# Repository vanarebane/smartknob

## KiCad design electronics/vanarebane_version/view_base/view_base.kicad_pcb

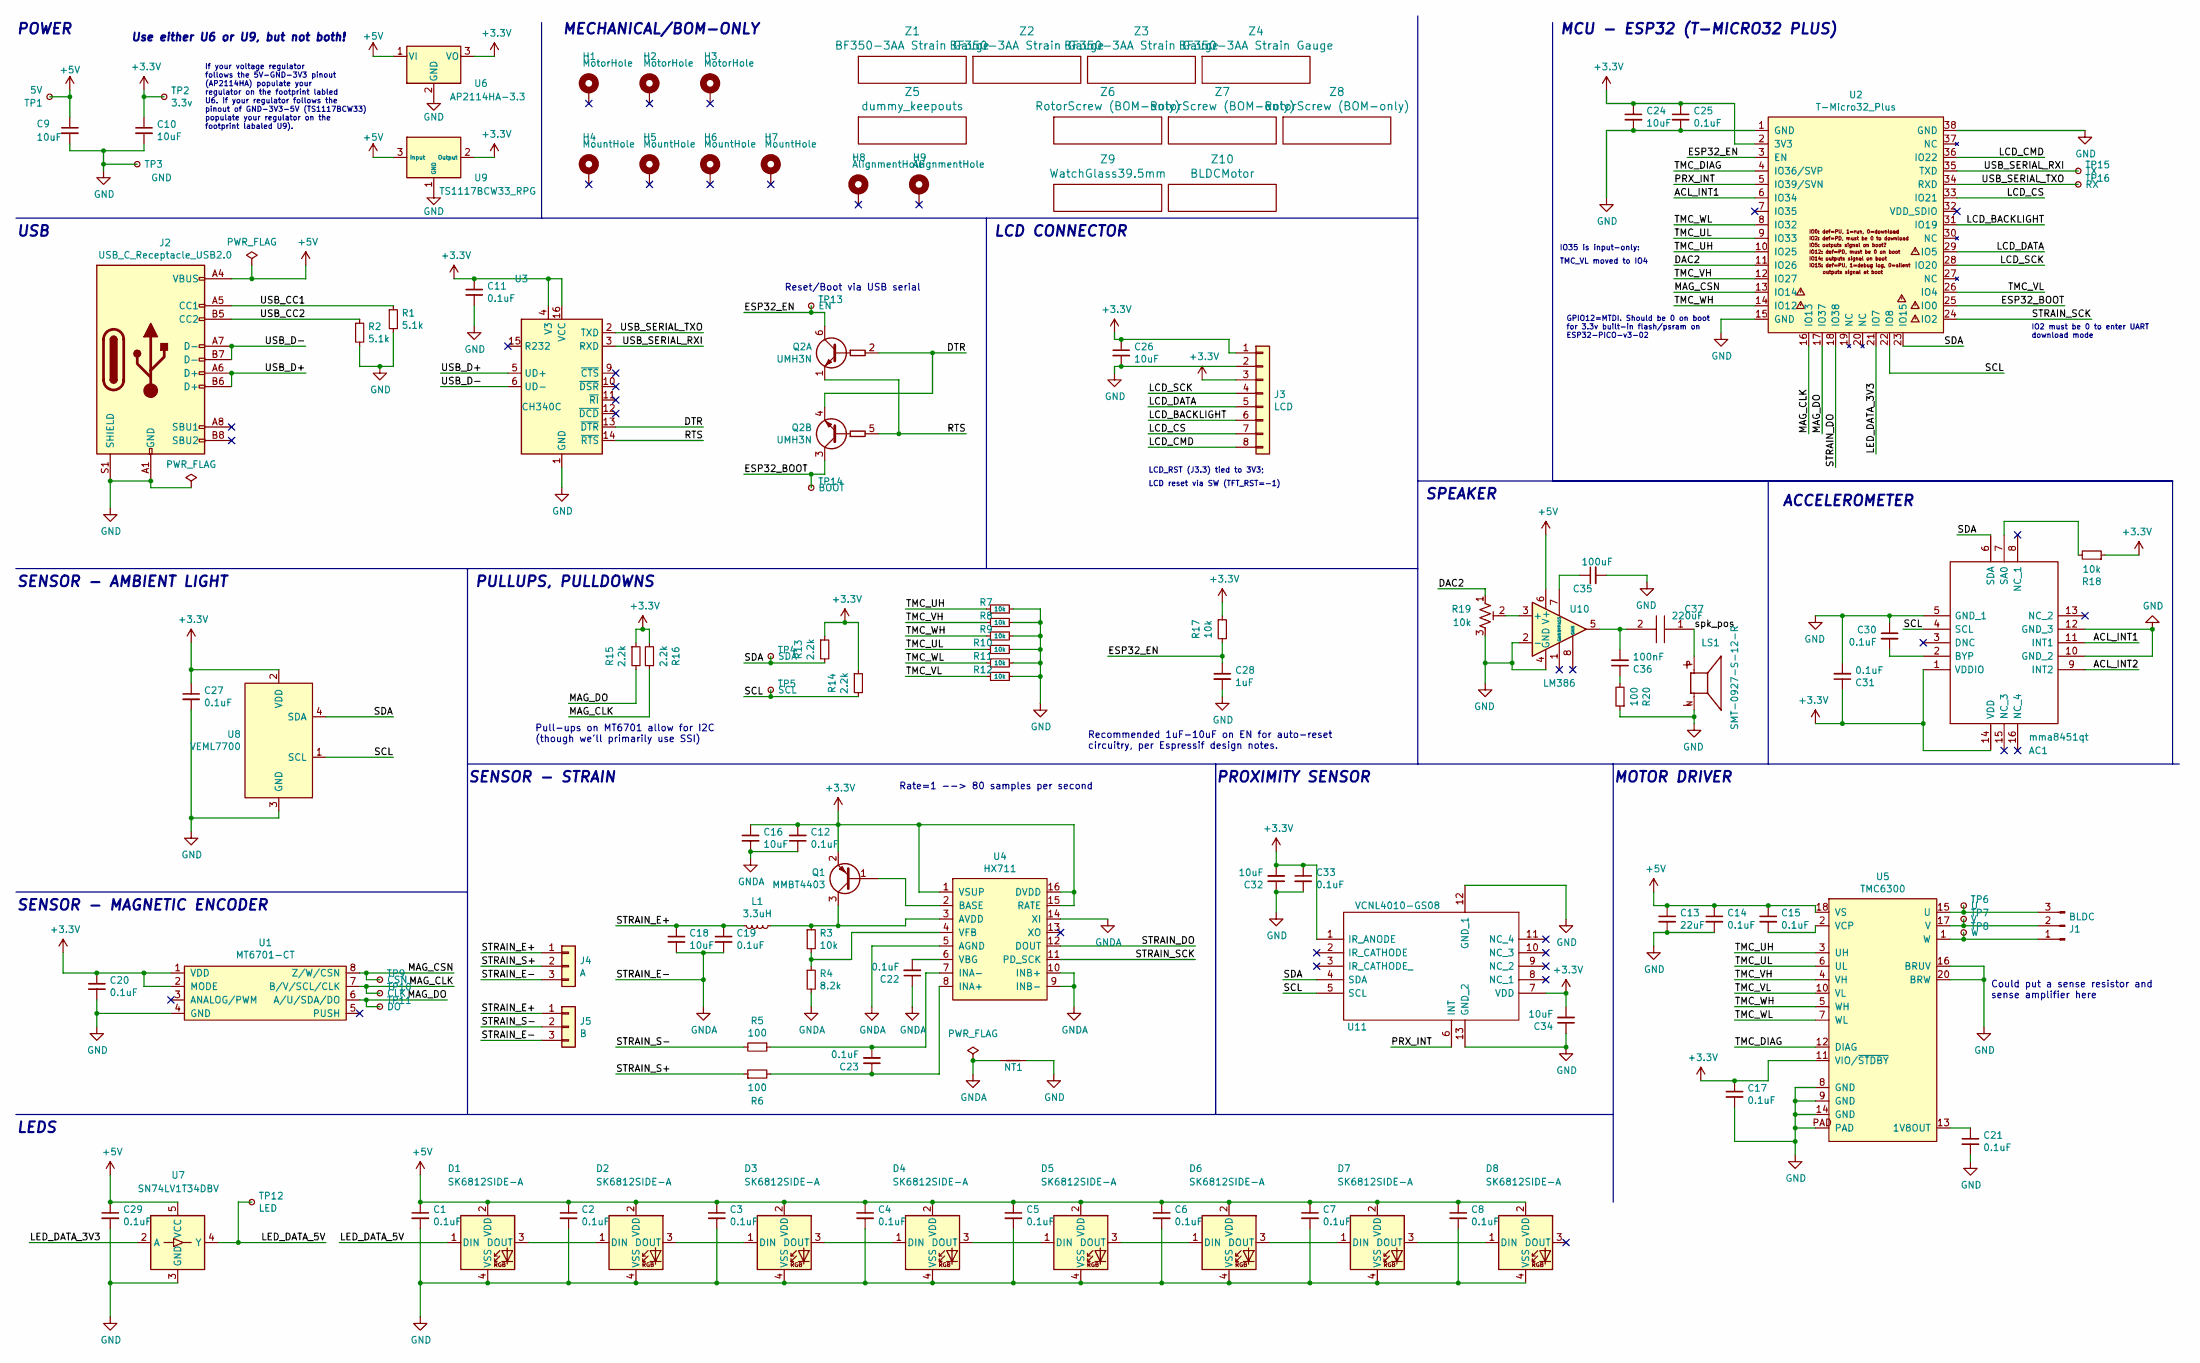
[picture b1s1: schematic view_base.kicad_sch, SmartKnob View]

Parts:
AC1: mma8451qt; PQFN50P300X300X100-16N; Mouser Part Number 841-MMA8451QT
C1, C2, C3, C4, C5, C6, C7, C8, C11, C12, C14, C15, C17, C19, C20, C21, C22, C23, C25, C27, C29, C30, C31, C33: 0.1uF; C_0603_1608Metric; LCSC C1591
C9, C10, C16, C18, C24, C26, C32, C34: 10uF; C_0805_2012Metric; LCSC C2922480
C13: 22uF; C_0805_2012Metric; LCSC C98190
C28: 1uF; C_0603_1608Metric; Mouser 187-CL10A105KA8NNNC
C35: 100uF; C_0603_1608Metric; LCSC C1591
C36: 100nF; C_0603_1608Metric; LCSC C1591
C37: 220uF; CAPAE660X850N; Manufacturer_Part_Number AEF0608221M006R
D1, D2, D3, D4, D5, D6, D7, D8: SK6812SIDE-A; SK6812-SIDE-A; Digikey 1528-4691-ND
H1, H2, H3: MotorHole; MountingHole_M1.6; LCSC C2931389
H4, H5, H6, H7: MountHole; MountingHole_2.2mm_M2_ISO7380_Pad_NonVirtual; LCSC C2911210 or C2911532 (screw), C2961595 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
H8, H9: AlignmentHole; MountingHole_2.2mm_M2_ISO7380_Pad_NonVirtual
J1: BLDC; 532610371; LCSC C293630
J2: USB_C_Receptacle_USB2.0; USB_C_Receptacle_Palconn_UTC16-G; LCSC C428463
J3: LCD; SolderPads_2mm_8
J4: A; SolderPads_2mm_3_STRAIN
J5: B; SolderPads_2mm_3_STRAIN
L1: 3.3uH; L_0805_2012Metric; LCSC C307744
LS1: SMT-0927-S-12-R; XDCR_SMT-0927-S-12-R; PARTREV 1/19/2017
NT1: NetTie_2; NetTie-2_SMD_Pad0.5mm
Q1: MMBT4403; SOT-23; LCSC C78864
Q2: UMH3N; SOT-363_SC-70-6; LCSC C62892
R1, R2: 5.1k; R_0603_1608Metric; LCSC C105580
R3, R7, R8, R9, R10, R11, R12, R17, R18: 10k; R_0603_1608Metric; LCSC C98220
R4: 8.2k; R_0603_1608Metric; LCSC C114637
R5, R6, R20: 100; R_0603_1608Metric; LCSC C319953
R13, R14, R15, R16: 2.2k; R_0603_1608Metric; LCSC C4190
R19: 10k; Potentiometer_Bourns_3214J_Horizontal
TP1: 5V; TestPoint_Pad_D2.0mm_ValueSilk
TP2: 3.3v; TestPoint_Pad_D2.0mm_ValueSilk
TP3: GND; TestPoint_Pad_D2.0mm_ValueSilk
TP4: SDA; TestPoint_Pad_D2.0mm_ValueSilk
TP5: SCL; TestPoint_Pad_D2.0mm_ValueSilk
TP6: U; TestPoint_Pad_D2.0mm_ValueSilk
TP7: V; TestPoint_Pad_D2.0mm_ValueSilk
TP8: W; TestPoint_Pad_D2.0mm_ValueSilk
TP9: CSN; TestPoint_Pad_D2.0mm_ValueSilk
TP10: CLK; TestPoint_Pad_D2.0mm_ValueSilk
TP11: DO; TestPoint_Pad_D2.0mm_ValueSilk
TP12: LED; TestPoint_Pad_D2.0mm_ValueSilk
TP13: EN; TestPoint_Pad_D2.0mm_ValueSilk
TP14: BOOT; TestPoint_Pad_D2.0mm_ValueSilk
TP15: TX; TestPoint_Pad_D2.0mm_ValueSilk
TP16: RX; TestPoint_Pad_D2.0mm_ValueSilk
U1: MT6701-CT; SOIC-8_3.9x4.9mm_P1.27mm; LCSC C2856764, or C3003196
U2: T-Micro32_Plus; T-Micro32; Digikey N/A
U3: CH340C; SOIC-16_3.9x9.9mm_P1.27mm; LCSC C84681
U4: HX711; SOIC-16_3.9x9.9mm_P1.27mm; LCSC C43656
U5: TMC6300; QFN-20-1EP_3x3mm_P0.4mm_EP1.65x1.65mm_ThermalVias_LargerVia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; Digikey TMC6300-LA-T
U6: AP2114HA-3.3; SOT-223-3_TabPin2; LCSC C460314
U7: SN74LV1T34DBV; SOT-23-5; LCSC C100024
U8: VEML7700; VEML7700-TOP; Digikey VEML7700-TT
U9: TS1117BCW33_RPG; SOT-223-3_TabPin2; LCSC C6186, C35879, or others
U10: LM386; SOIC-8_3.9x4.9mm_P1.27mm
U11: VCNL4010-GS08; VCNL4010GS08; Mouser Part Number 78-VCNL4010-GS08
Z1, Z2, Z3, Z4: BF350-3AA Strain Gauge; BF350-3AA; Digikey N/A
Z5: dummy_keepouts; ViewKeepouts3d
Z6, Z7, Z8: RotorScrew (BOM-only); bom_only_no_pin
Z9: WatchGlass39.5mm; bom_only_no_pin
Z10: BLDCMotor; bom_only_no_pin

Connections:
+3.3V: AC1.1 (VDDIO), AC1.14 (VDD), C10.1, C11.1, C12.1, C16.1, C17.1, C20.1, C24.1, C25.1, C26.1, C27.1, C31.1, C32.2, C33.1, C34.2, J3.1, J3.3, Q1.2 (E), R13.1, R14.1, R15.1, R16.2, R17.1, R18.1, TP2.1, U1.1 (VDD), U1.2 (MODE), U2.2 (3V3), U3.4 (V3), U3.16 (VCC), U4.1 (VSUP), U4.15 (RATE), U4.16 (DVDD), U5.11 (VIO/~STDBY), U6.3 (VO), U8.2 (VDD), U9.2 (Output), U11.1 (IR_ANODE), U11.7 (VDD)
+5V: C1.1, C2.1, C3.1, C4.1, C5.1, C6.1, C7.1, C8.1, C9.1, C13.1, C14.1, C15.1, C29.1, D1.2 (VDD), D2.2 (VDD), D3.2 (VDD), D4.2 (VDD), D5.2 (VDD), D6.2 (VDD), D7.2 (VDD), D8.2 (VDD), J2.A4 (VBUS), J2.A9 (VBUS), J2.B4 (VBUS), J2.B9 (VBUS), TP1.1, U5.18 (VS), U6.1 (VI), U7.5 (VCC), U9.3 (Input), U10.6 (V+)
/ACL_INT1: AC1.11 (INT1), U2.6 (IO34)
/ACL_INT2: AC1.9 (INT2)
/DAC2: R19.1, U2.11 (IO26)
/DTR: Q2.2 (B1), Q2.4 (E2), U3.13 (~DTR)
/ESP32_BOOT: Q2.3 (C2), TP14.1, U2.25 (IO0)
/ESP32_EN: C28.1, Q2.6 (C1), R17.2, TP13.1, U2.3 (EN)
/LCD_BACKLIGHT: J3.6, U2.31 (IO19)
/LCD_CMD: J3.8, U2.36 (IO22)
/LCD_CS: J3.7, U2.33 (IO21)
/LCD_DATA: J3.5, U2.29 (IO5)
/LCD_SCK: J3.4, U2.28 (IO20)
/LED_DATA_3V3: U2.21 (IO7), U7.2 (A)
/LED_DATA_5V: D1.1 (DIN), TP12.1, U7.4 (Y)
/MAG_CLK: R16.1, TP10.1, U1.7 (B/V/SCL/CLK), U2.16 (IO13)
/MAG_CSN: TP9.1, U1.8 (Z/W/CSN), U2.13 (IO14)
/MAG_DO: R15.2, TP11.1, U1.6 (A/U/SDA/DO), U2.17 (IO37)
/PRX_INT: U2.5 (IO39/SVN), U11.6 (INT)
/RTS: Q2.1 (E1), Q2.5 (B2), U3.14 (~RTS)
/SCL: AC1.4 (SCL), R14.2, TP5.1, U2.22 (IO8), U8.1 (SCL), U11.5 (SCL)
/SDA: AC1.6 (SDA), R13.2, TP4.1, U2.23 (IO15), U8.4 (SDA), U11.4 (SDA)
/STRAIN_DO: U2.18 (IO38), U4.12 (DOUT)
/STRAIN_E+: C18.1, C19.1, J4.1, J5.1, L1.2
/STRAIN_S+: J4.2, R6.1
/STRAIN_S-: J5.2, R5.2
/STRAIN_SCK: U2.24 (IO2), U4.11 (PD_SCK)
/TMC_DIAG: U2.4 (IO36/SVP), U5.12 (DIAG)
/TMC_UH: R7.1, U2.10 (IO25), U5.3 (UH)
/TMC_UL: R10.1, U2.9 (IO33), U5.6 (UL)
/TMC_VH: R8.1, U2.12 (IO27), U5.4 (VH)
/TMC_VL: R12.1, U2.26 (IO4), U5.10 (VL)
/TMC_WH: R9.1, U2.14 (IO12), U5.5 (WH)
/TMC_WL: R11.1, U2.8 (IO32), U5.7 (WL)
/USB_CC1: J2.A5 (CC1), R1.1
/USB_CC2: J2.B5 (CC2), R2.1
/USB_D+: J2.A6 (D+), J2.B6 (D+), U3.5 (UD+)
/USB_D-: J2.A7 (D-), J2.B7 (D-), U3.6 (UD-)
/USB_SERIAL_RXI: TP15.1, U2.35 (TXD), U3.3 (RXD)
/USB_SERIAL_TXO: TP16.1, U2.34 (RXD), U3.2 (TXD)
GND: AC1.5 (GND_1), AC1.10 (GND_2), AC1.12 (GND_3), C1.2, C2.2, C3.2, C4.2, C5.2, C6.2, C7.2, C8.2, C9.2, C10.2, C11.2, C13.2, C14.2, C17.2, C20.2, C21.2, C24.2, C25.2, C26.2, C27.2, C28.2, C29.2, C30.1, C31.2, C32.1, C33.2, C34.1, C35.2, D1.4 (VSS), D2.4 (VSS), D3.4 (VSS), D4.4 (VSS), D5.4 (VSS), D6.4 (VSS), D7.4 (VSS), D8.4 (VSS), J2.A1 (GND), J2.A12 (GND), J2.B1 (GND), J2.B12 (GND), J2.S1 (SHIELD), J3.2, LS1.N, NT1.2, R1.2, R2.2, R7.2, R8.2, R9.2, R10.2, R11.2, R12.2, R19.3, R20.1, TP3.1, U1.4 (GND), U2.1 (GND), U2.15 (GND), U2.38 (GND), U3.1 (GND), U5.8 (GND), U5.9 (GND), U5.14 (GND), U5.16 (BRUV), U5.20 (BRW), U5.PAD, U6.2 (GND), U7.3 (GND), U8.3 (GND), U9.1 (GND), U10.2 (-), U10.4 (GND), U11.12 (GND_1), U11.13 (GND_2)
GNDA: C12.2, C16.2, C18.2, C19.2, C22.1, J4.3, J5.3, NT1.1, R4.2, U4.5 (AGND), U4.9 (INB-), U4.10 (INB+), U4.14 (XI)
unnamed: AC1.2 (BYP), C30.2
unnamed: AC1.7 (SA0), R18.2
unnamed: C15.2, U5.2 (VCP)
unnamed: C21.1, U5.13 (1V8OUT)
unnamed: C22.2, U4.6 (VBG)
unnamed: C23.1, R6.2, U4.8 (INA+)
unnamed: C23.2, R5.1, U4.7 (INA-)
unnamed: C35.1, U10.7 (BYPASS)
unnamed: C36.1, R20.2
unnamed: C36.2, C37.2, U10.5
unnamed: D1.3 (DOUT), D2.1 (DIN)
unnamed: D2.3 (DOUT), D3.1 (DIN)
unnamed: D3.3 (DOUT), D4.1 (DIN)
unnamed: D4.3 (DOUT), D5.1 (DIN)
unnamed: D5.3 (DOUT), D6.1 (DIN)
unnamed: D6.3 (DOUT), D7.1 (DIN)
unnamed: D7.3 (DOUT), D8.1 (DIN)
unnamed: J1.1, TP8.1, U5.1 (W)
unnamed: J1.2, TP7.1, U5.17 (V)
unnamed: J1.3, TP6.1, U5.15 (U)
unnamed: L1.1, Q1.3 (C), R3.1, U4.3 (AVDD)
unnamed: C37.1, LS1.P
unnamed: Q1.1 (B), U4.2 (BASE)
unnamed: R3.2, R4.1, U4.4 (VFB)
unnamed: R19.2, U10.3 (+)

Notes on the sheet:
IO35 is input-only:
TMC_VL moved to IO4
LCD_RST (J3.3) tied to 3V3;
LCD reset via SW (TFT_RST=-1)
POWER
SPEAKER
Could put a sense resistor and sense amplifier here
MCU - ESP32 (T-MICRO32 PLUS)
If your voltage regulator follows the 5V-GND-3V3 pinout (AP2114HA) populate your regulator on the footprint labled U6. If your regulator follows the pinout of GND-3V3-5V (TS1117BCW33) populate your regulator on the footprint labaled U9).
SENSOR - MAGNETIC ENCODER
MOTOR DRIVER
ACCELEROMETER
MECHANICAL/BOM-ONLY
IO2 must be 0 to enter UART download mode
GPIO12=MTDI. Should be 0 on boot for 3.3v built-in flash/psram on ESP32-PICO-v3-02
Pull-ups on MT6701 allow for I2C (though we'll primarily use SSI)
Use either U6 or U9, but not both!
Rate=1 --> 80 samples per second
SENSOR - AMBIENT LIGHT
Recommended 1uF-10uF on EN for auto-reset circuitry, per Espressif design notes.
USB
SENSOR - STRAIN
LEDS
PROXIMITY SENSOR
PULLUPS, PULLDOWNS
LCD CONNECTOR
Reset/Boot via USB serial

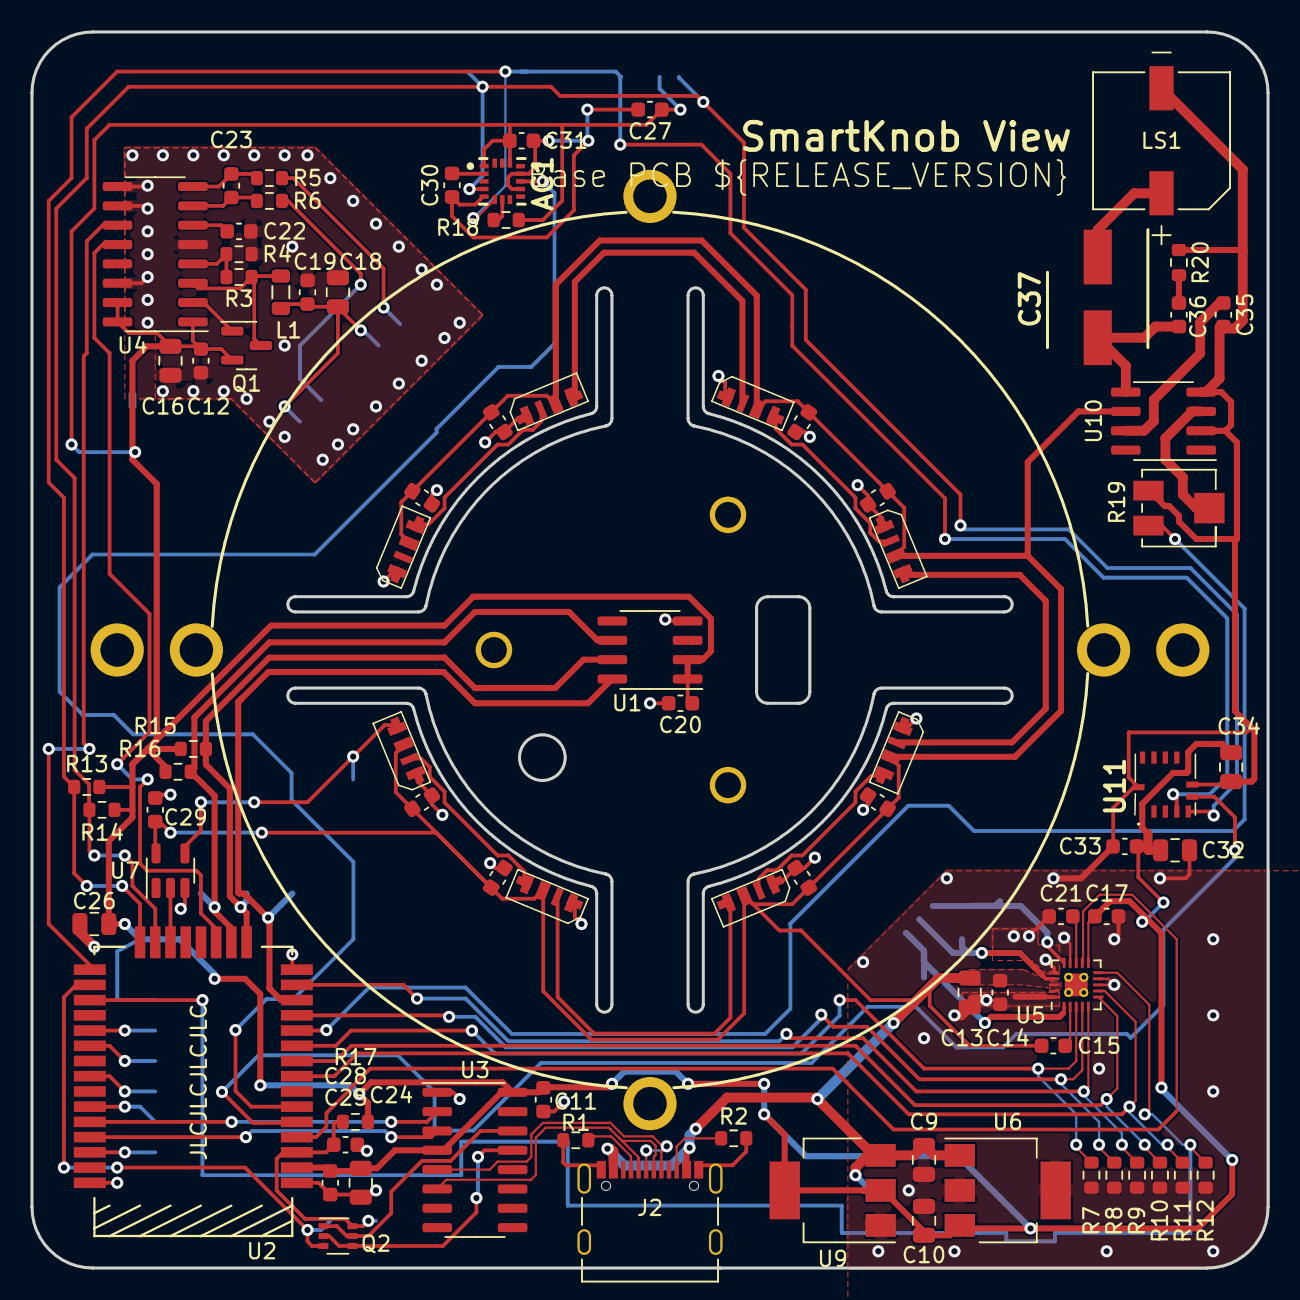
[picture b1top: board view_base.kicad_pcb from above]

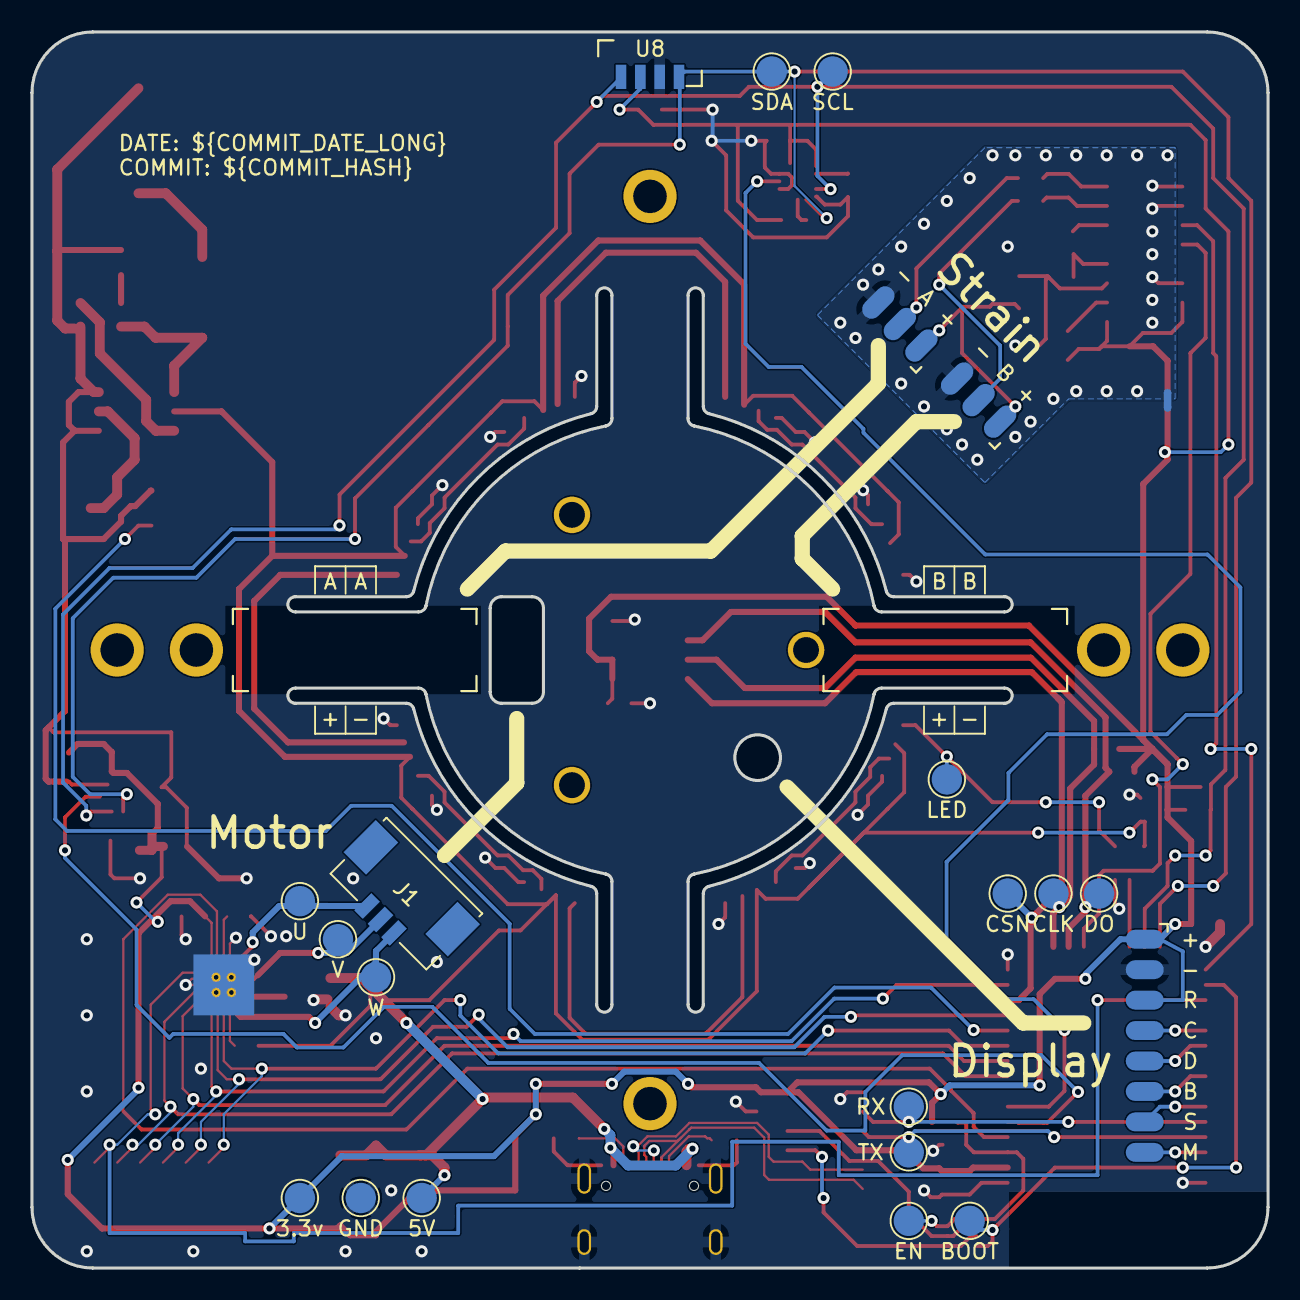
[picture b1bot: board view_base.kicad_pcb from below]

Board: 2 copper layers, 81.2 x 81.2 mm, 122 parts (26 on the bottom side), 66 nets.

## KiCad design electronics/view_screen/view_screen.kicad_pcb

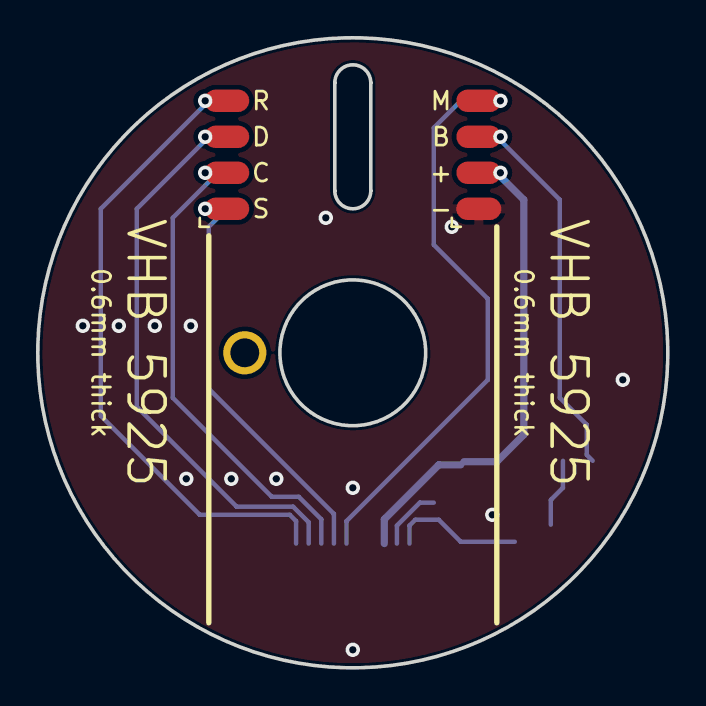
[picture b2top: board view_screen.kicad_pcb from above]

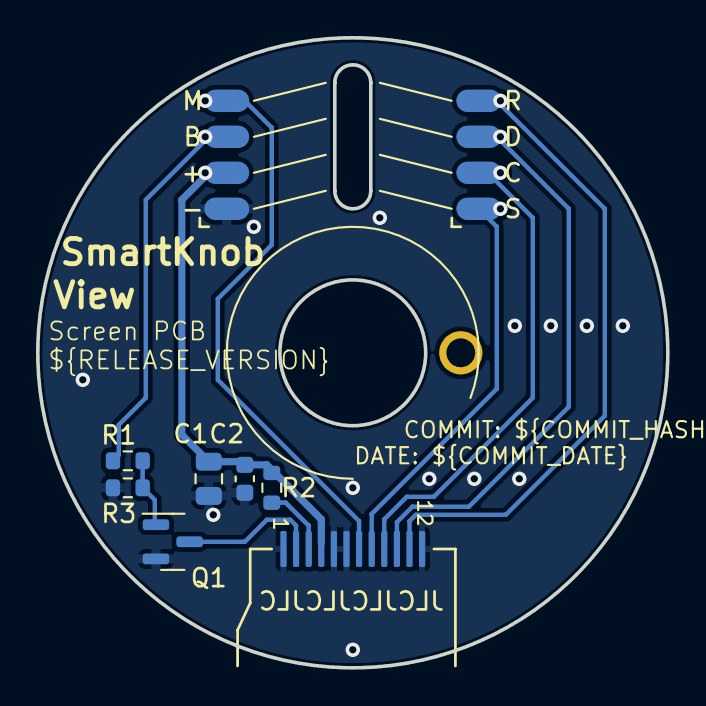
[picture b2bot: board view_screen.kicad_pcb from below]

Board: 2 copper layers, 35.0 x 35.0 mm, 12 parts (9 on the bottom side), 11 nets.

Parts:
C1: 22uF; C_0805_2012Metric
C2: 0.1uF; C_0603_1608Metric
H1: AlignmentHole; AlignmentHole_1.6
J1, J3, J4, J5: Conn_01x04; SolderPads_2mm_4
J2: GC9A01; GC9A01Round1.28
Q1: 2N7002; SOT-23
R1: 10k; R_0603_1608Metric
R2: 22R; R_0603_1608Metric
R3: 1M; R_0603_1608Metric

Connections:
/BACKLIGHT_EN: J1.3, J4.3, R1.1
/DC: J1.4, J2.7, J4.4
/LEDA: J2.3, R2.2
/LEDK: J2.2, Q1.3 (D)
/MOSI: J2.10, J3.3, J5.3
/SCK: J2.9, J3.2, J5.2
/VDD: C1.1, C2.1, J1.2, J2.4, J4.2, R2.1
/nCS: J2.8, J3.1, J5.1
/nRESET: J2.11, J3.4, J5.4
GND: C1.2, C2.2, J1.1, J2.1, J2.5, J2.6, J2.12, J4.1, Q1.2 (S), R3.2
unnamed: Q1.1 (G), R1.2, R3.1

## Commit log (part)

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2022-11-30 change USB tpye-c port
2023-01-11 Added proximity and accelerator sensor
2025-02-13 Rename .gitmodules to temp.gitmodules
    Cloning git hangs at this point
2025-02-13 move schematic folder
2025-02-24 Started BLE
2025-02-24 browser integration
2025-02-24 browser files
2025-02-24 Rename .gitmodules to .gitmodules_bad
2025-02-24 Rename .gitmodules_bad to .gitmodules
2025-02-24 BLE dev
2025-02-25 made SmartKnob JS class
2025-02-25 reverted back to old BLE lib - works well with only one characteristic
2025-02-27 progress
2025-02-27 Almost
2025-02-27 just some hours closer to death
2025-02-28 BLE some values correct / button added: works / started with onWrite()
2025-02-28 sending value established - needs formating
2025-03-01 BLE almost works - some JS errors in browser
2025-03-01 BLE read/write fixed
2025-03-02 BLE fixed
2025-03-02 BLE fixed - Motor 98%
2025-03-02 forgot to style changelog
2025-03-08 Sub value and Motor config implemented
    Needs firmware update
2025-03-08 Web responsive part, some finetuning
2025-03-09 Fixed width

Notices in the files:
parts and their libraries:
Copyright 2021 Accelerated Designs. All rights reserved.
